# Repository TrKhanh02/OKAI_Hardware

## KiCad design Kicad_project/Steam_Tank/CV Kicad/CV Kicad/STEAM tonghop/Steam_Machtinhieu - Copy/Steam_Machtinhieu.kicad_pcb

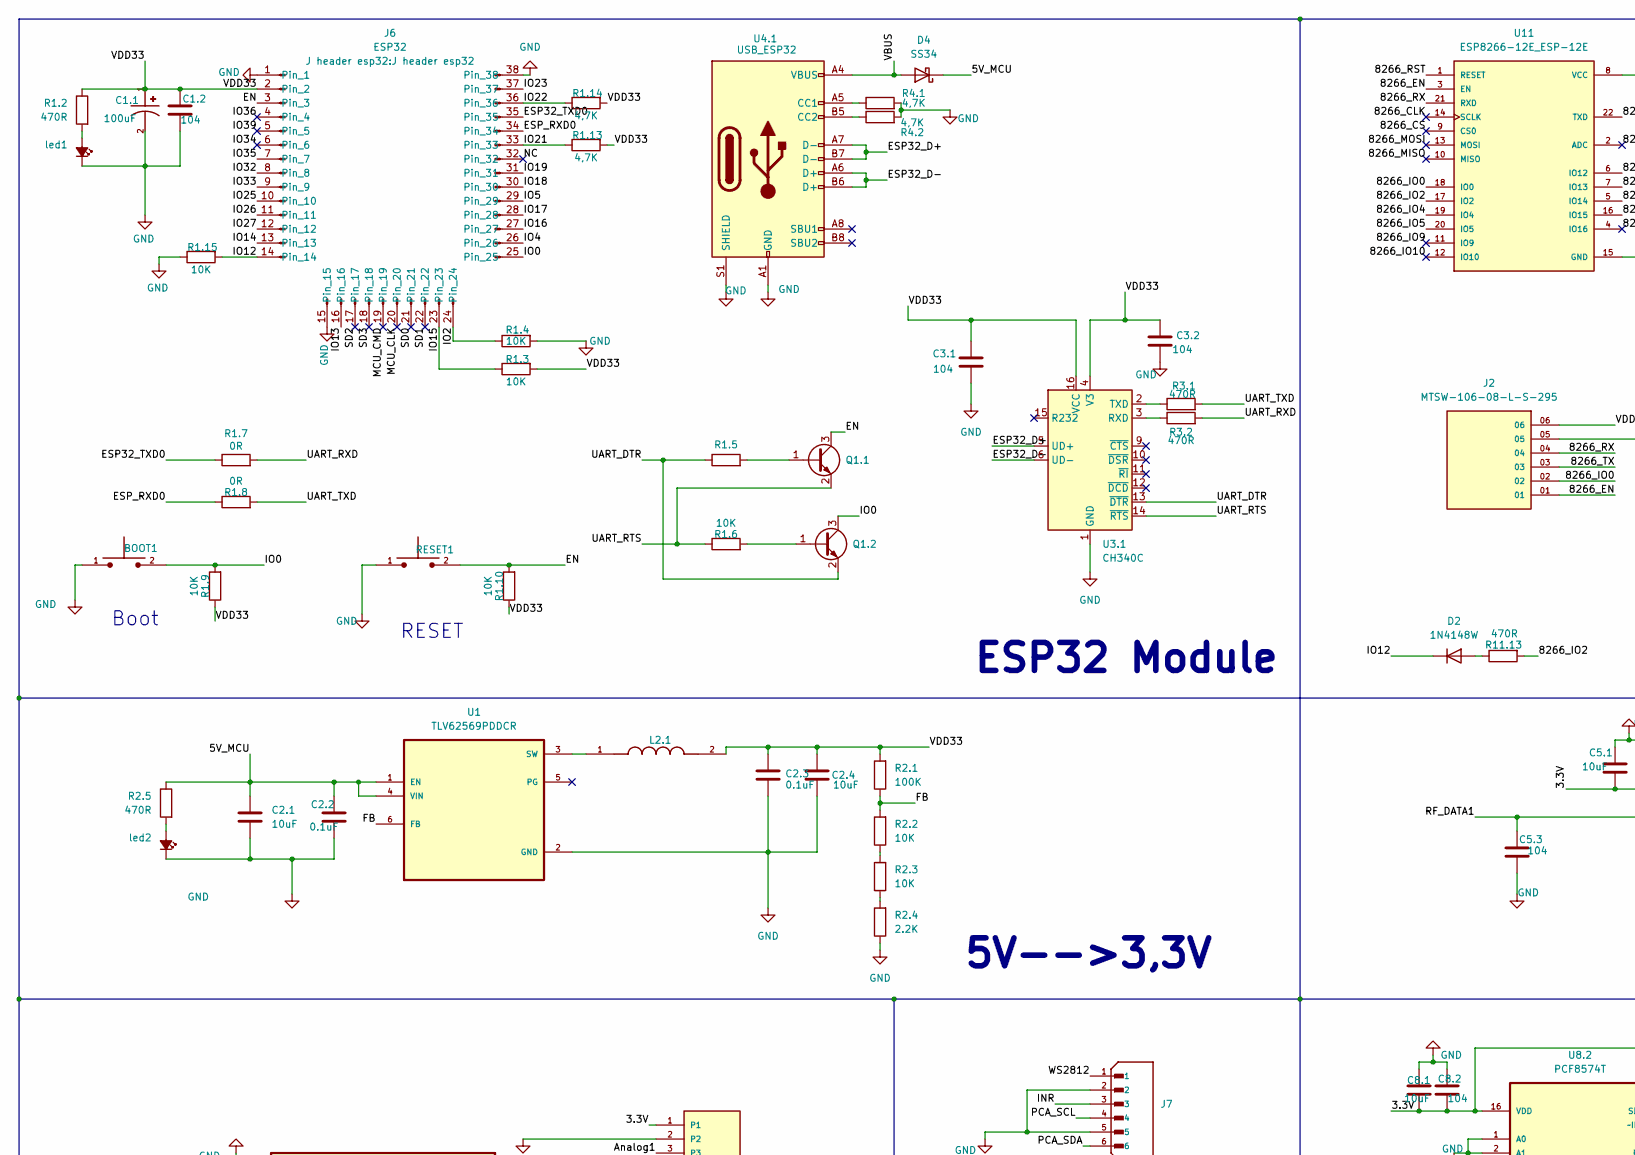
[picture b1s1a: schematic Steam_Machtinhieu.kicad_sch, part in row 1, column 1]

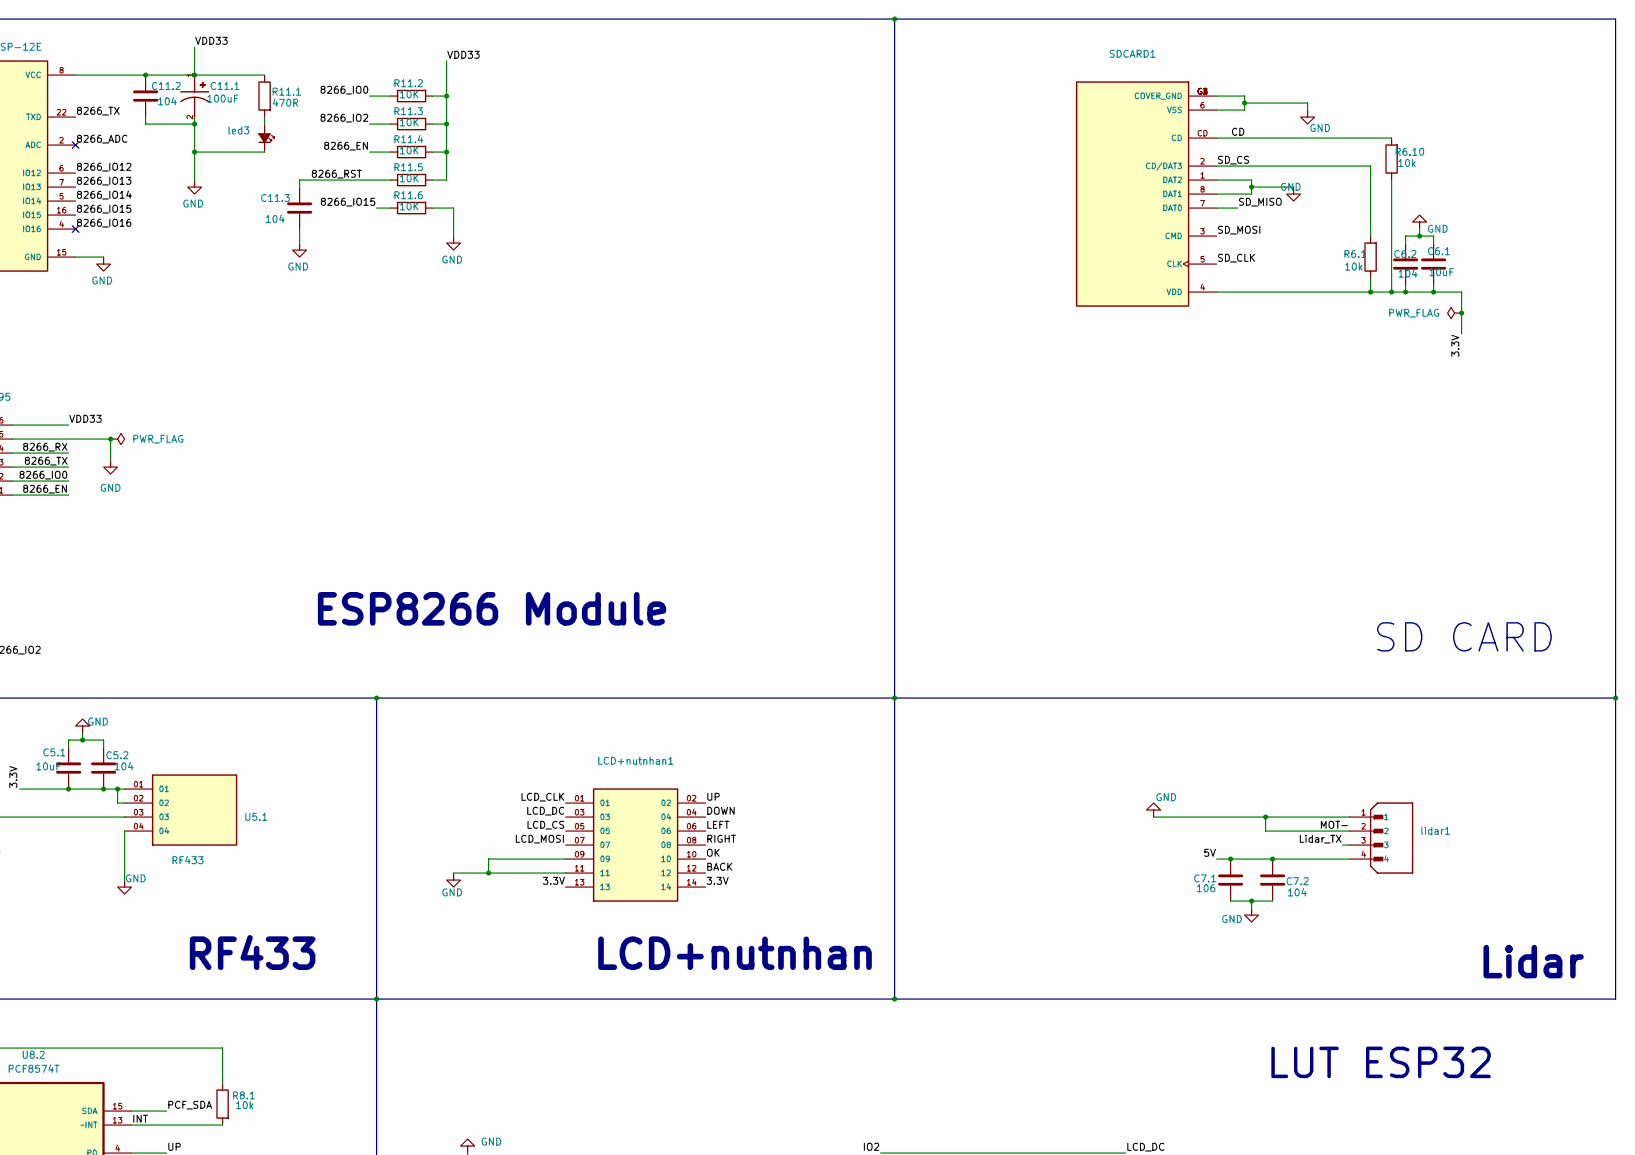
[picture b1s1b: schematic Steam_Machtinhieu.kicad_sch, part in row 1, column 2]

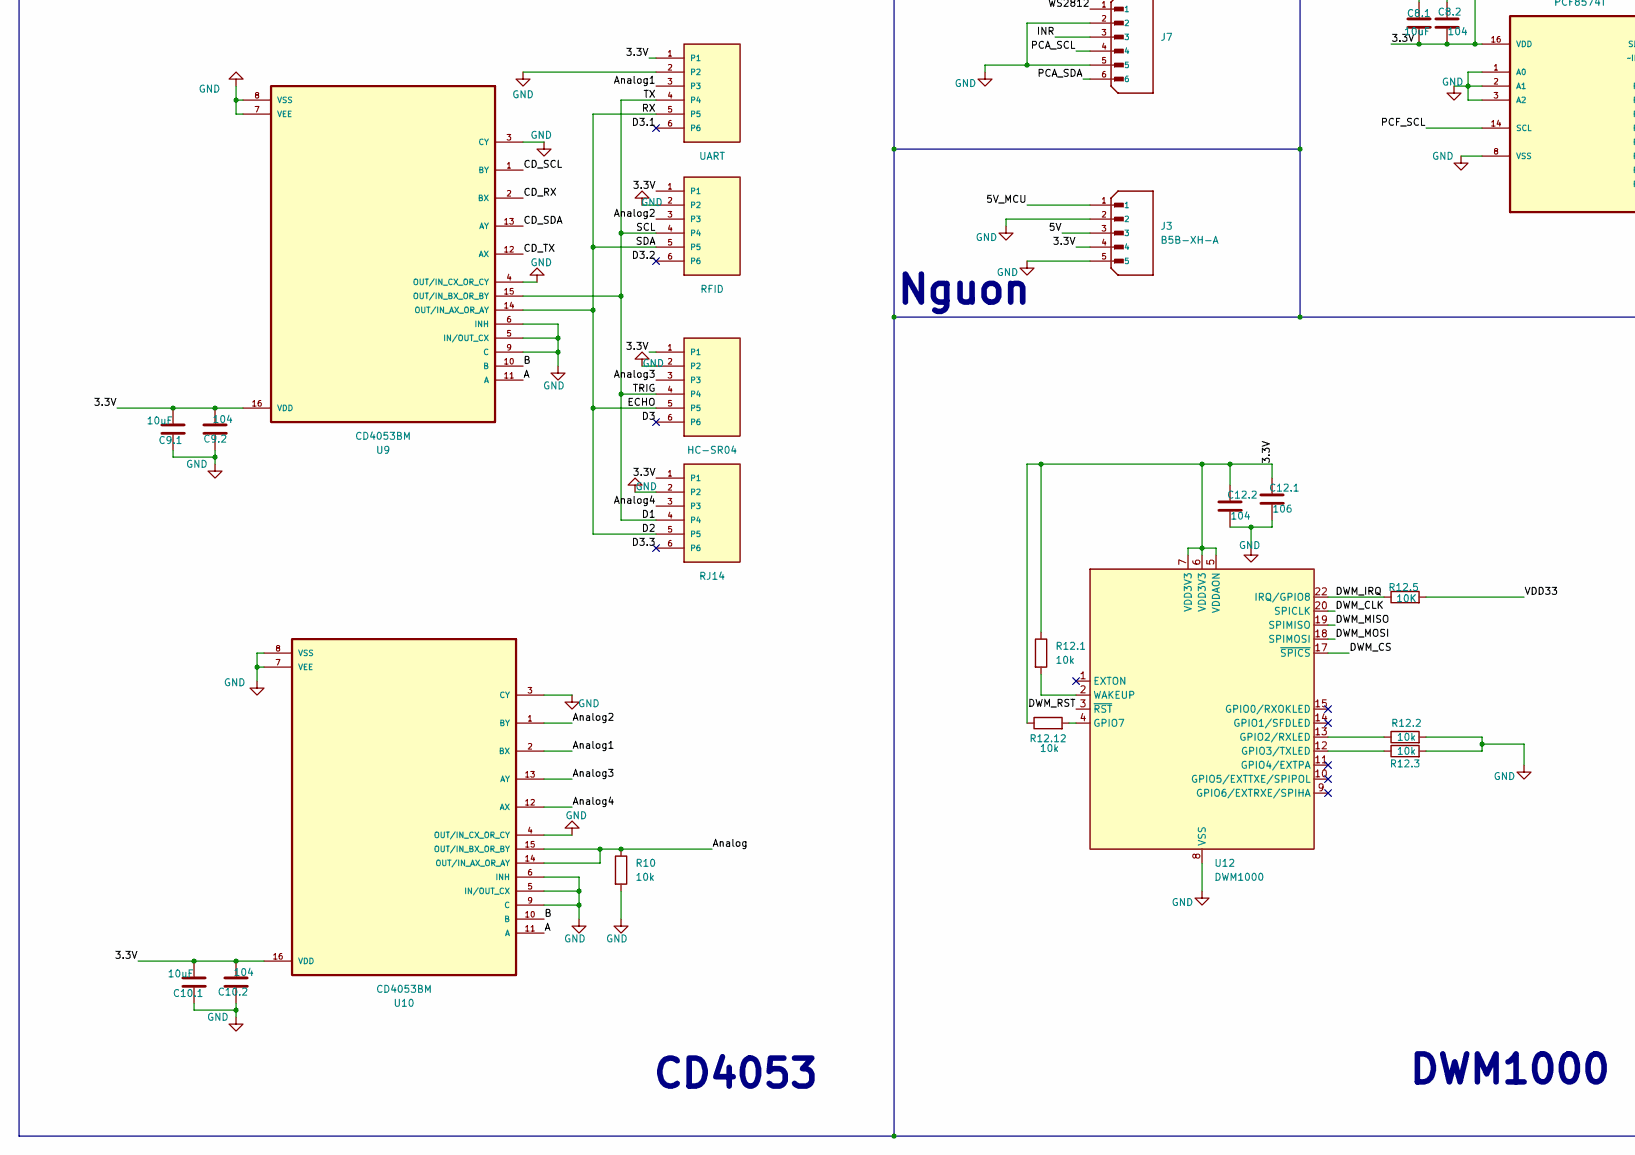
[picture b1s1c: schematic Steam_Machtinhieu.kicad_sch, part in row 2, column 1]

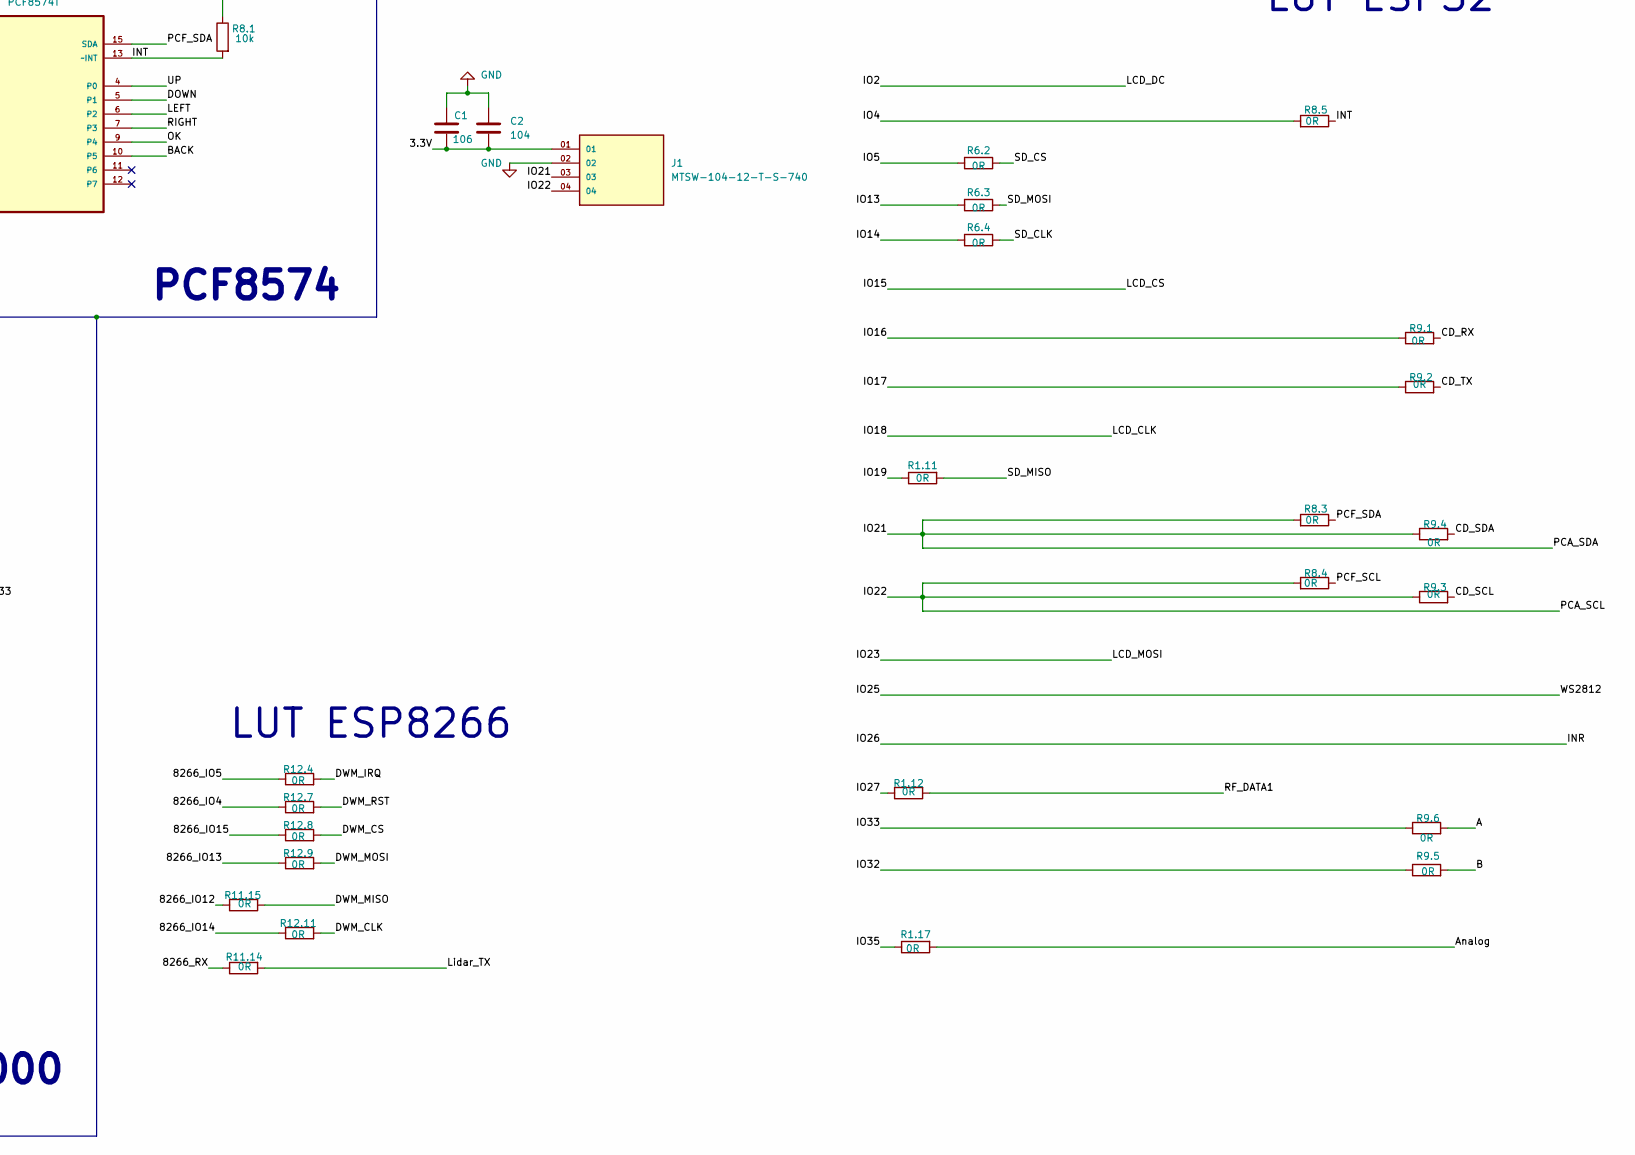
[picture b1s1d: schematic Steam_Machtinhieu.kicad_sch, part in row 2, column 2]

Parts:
BOOT1: TS10-63-26-BE-250-SMT-TR; SW_TS10-63-26-BE-250-SMT-TR; PARTREV 1.0
C1, C7.1, C12.1: 106; C_0805_2012Metric_Pad1.18x1.45mm_HandSolder
C1.1, C11.1: 100uF; CAPMP3216X180N; PARTREV 031320
C1.2, C2, C3.1, C3.2, C5.2, C5.3, C6.2, C7.2, C8.2, C9.2, C10.2, C11.2, C11.3, C12.2: 104; C_0805_2012Metric_Pad1.18x1.45mm_HandSolder
C2.1, C2.4: 10uF; C_0805_2012Metric
C2.2, C2.3: 0.1uF; C_0805_2012Metric
C5.1, C6.1, C8.1, C9.1, C10.1: 10uF; C_0805_2012Metric_Pad1.18x1.45mm_HandSolder
D2: 1N4148W; D_SOD-123
D4: SS34; D_SMA
J1: MTSW-104-12-T-S-740; SAMTEC_MTSW-104-12-T-S-740; PARTREV R
J2: MTSW-106-08-L-S-295; SAMTEC_MTSW-106-08-L-S-295; PARTREV R
J3: B5B-XH-A; JST_B5B-XH-A; PARTREV 7/4/21
J6: ESP32; J header esp32
J7: B6B-XH-A_LF__SN_; JST_B6B-XH-A_LF__SN_; PARTREV 7/4/21
L2.1: SLF7032T-331MR22-2PF; IND_SLF7032T-331MR22-2PF; PARTREV N/A
LCD+nutnhan1: MTLW-107-07-G-D-230; SAMTEC_MTLW-107-07-G-D-230; PARTREV R
Q1.1, Q1.2: SS8050; SOT-23
R1.2, R2.5, R3.1, R3.2, R11.1, R11.13: 470R; R_0805_2012Metric_Pad1.20x1.40mm_HandSolder
R1.3, R1.4, R1.5, R1.6, R1.9, R1.10, R1.15, R11.2, R11.3, R11.4, R11.5, R11.6, R12.5: 10K; R_0805_2012Metric_Pad1.20x1.40mm_HandSolder
R1.7, R1.8, R1.11, R1.12, R1.17, R6.2, R6.3, R6.4, R8.3, R8.4, R8.5, R9.1, R9.2, R9.3, R9.4, R9.5, R9.6, R11.14, R11.15, R12.4, R12.7, R12.8, R12.9, R12.11: 0R; R_0805_2012Metric_Pad1.20x1.40mm_HandSolder
R1.13, R1.14, R4.1, R4.2: 4,7K; R_0805_2012Metric_Pad1.20x1.40mm_HandSolder
R2.1: 100K; R_0805_2012Metric
R2.2, R2.3: 10K; R_0805_2012Metric
R2.4: 2.2K; R_0805_2012Metric
R6.1, R6.10, R8.1, R10, R12.1, R12.2, R12.3, R12.12: 10k; R_0805_2012Metric_Pad1.20x1.40mm_HandSolder
R11: UART; TE_RJ11-6N-B; PART_DESCRIPTION CONN MOD JACK 6P6C R/A UNSHLD
R12: RFID; TE_RJ11-6N-B; PART_DESCRIPTION CONN MOD JACK 6P6C R/A UNSHLD
RESET1: TS10-63-26-BE-250-SMT-TR; SW_TS10-63-26-BE-250-SMT-TR; PARTREV 1.0
RF433: U5.1; SAMTEC_MTSW-104-12-T-S-740; PARTREV R
RJ13, RJ14: HC-SR04; TE_RJ11-6N-B; PART_DESCRIPTION CONN MOD JACK 6P6C R/A UNSHLD
SDCARD1: MSD-1-A; CUI_MSD-1-A; PARTREV 1.0
U1: TLV62569PDDCR; SOT95P280X110-6N
U3.1: CH340C; SOIC-16_3.9x9.9mm_P1.27mm
U4.1: USB_ESP32; USB_C_Receptacle_HRO_TYPE-C-31-M-12
U8.2: PCF8574T; SOIC127P1032X265-16N; MPN PCF8574T
U9, U10: CD4053BM; SOIC127P600X175-16N
U11: ESP8266-12E_ESP-12E; XCVR_ESP8266-12E_ESP-12E
U12: DWM1000
led1, led2, led3: LED_Small_Filled; LED_0805_2012Metric_Pad1.15x1.40mm_HandSolder
lidar1: B4B-XH-A; JST_B4B-XH-A; PARTREV 7/4/21

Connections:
/3.3V: C1.2, C2.2, C5.1.2, C5.2.2, C6.1.1, C6.2.1, C8.1.1, C8.2.1, C9.1.1, C9.2.1, C10.1.1, C10.2.1, C12.1.1, C12.2.1, J1.01, J3.4, LCD+nutnhan1.13, LCD+nutnhan1.14, R6.1.1, R6.10.1, R8.1.1, R11.1, R12.1, R12.1.1, R12.12.1, RF433.01, RF433.02, RJ13.1, RJ14.1, SDCARD1.4 (VDD), U8.2.16 (VDD), U9.16 (VDD), U10.16 (VDD), U12.5 (VDDAON), U12.6 (VDD3V3), U12.7 (VDD3V3)
/5V: C7.1.1, C7.2.1, J3.3, lidar1.4
/5V_MCU: C2.1.1, C2.2.1, D4.1 (K), J3.1, R2.5.1, U1.1 (EN), U1.4 (VIN)
/8266_ADC: U11.2 (ADC)
/8266_CLK: U11.14 (SCLK)
/8266_CS: U11.9 (CS0)
/8266_EN: J2.01, R11.4.1, U11.3 (EN)
/8266_IO0: J2.02, R11.2.1, U11.18 (IO0)
/8266_IO2: R11.3.1, R11.13.2, U11.17 (IO2)
/8266_IO4: R12.7.1, U11.19 (IO4)
/8266_IO5: R12.4.1, U11.20 (IO5)
/8266_IO9: U11.11 (IO9)
/8266_IO10: U11.12 (IO10)
/8266_IO12: R11.15.1, U11.6 (IO12)
/8266_IO13: R12.9.1, U11.7 (IO13)
/8266_IO14: R12.11.1, U11.5 (IO14)
/8266_IO15: R11.6.1, R12.8.1, U11.16 (IO15)
/8266_IO16: U11.4 (IO16)
/8266_MISO: U11.10 (MISO)
/8266_MOSI: U11.13 (MOSI)
/8266_RST: C11.3.1, R11.5.1, U11.1 (RESET)
/8266_RX: J2.04, R11.14.1, U11.21 (RXD)
/8266_TX: J2.03, U11.22 (TXD)
/A: R9.6.2, U9.11 (A), U10.11 (A)
/Analog: R1.17.2, R10.1, U10.14 (OUT/IN_AX_OR_AY), U10.15 (OUT/IN_BX_OR_BY)
/Analog1: R11.3, U10.2 (BX)
/Analog2: R12.3, U10.1 (BY)
/Analog3: RJ13.3, U10.13 (AY)
/Analog4: RJ14.3, U10.12 (AX)
/B: R9.5.2, U9.10 (B), U10.10 (B)
/BACK: LCD+nutnhan1.12, U8.2.10 (P5)
/CD: R6.10.2, SDCARD1.CD
/CD_RX: R9.1.2, U9.2 (BX)
/CD_SCL: R9.3.2, U9.1 (BY)
/CD_SDA: R9.4.2, U9.13 (AY)
/CD_TX: R9.2.2, U9.12 (AX)
/D1: R11.4, R12.4, RJ13.4, RJ14.4, U9.15 (OUT/IN_BX_OR_BY)
/D2: R11.5, R12.5, RJ13.5, RJ14.5, U9.14 (OUT/IN_AX_OR_AY)
/D3: RJ13.6
/D3.1: R11.6
/D3.2: R12.6
/D3.3: RJ14.6
/DOWN: LCD+nutnhan1.04, U8.2.5 (P1)
/DWM_CLK: R12.11.2, U12.20 (SPICLK)
/DWM_CS: R12.8.2, U12.17 (~SPICS)
/DWM_IRQ: R12.4.2, R12.5.1, U12.22 (IRQ/GPIO8)
/DWM_MISO: R11.15.2, U12.19 (SPIMISO)
/DWM_MOSI: R12.9.2, U12.18 (SPIMOSI)
/DWM_RST: R12.7.2, U12.3 (~RST)
/EN: J6.3, Q1.1.3 (C), R1.10.2, RESET1.2
/ESP32_D+: U3.1.5 (UD+), U4.1.A7 (D-), U4.1.B7 (D-)
/ESP32_D-: U3.1.6 (UD-), U4.1.A6 (D+), U4.1.B6 (D+)
/ESP32_TXD0: J6.35, R1.7.1
/ESP_RXD0: J6.34, R1.8.1
/FB: R2.1.1, R2.2.2, U1.6 (FB)
/INR: J6.11, J7.3
/INT: R8.1.2, R8.5.1, U8.2.13 (~INT)
/IO0: BOOT1.2, J6.25, Q1.2.3 (C), R1.9.2
/IO2: J6.24, LCD+nutnhan1.03, R1.4.1
/IO4: J6.26, R8.5.2
/IO5: J6.29, R6.2.2
/IO12: D2.1 (K), J6.14, R1.15.2
/IO13: J6.16, R6.3.2
/IO14: J6.13, R6.4.2
/IO15: J6.23, LCD+nutnhan1.05, R1.3.1
/IO16: J6.27, R9.1.1
/IO17: J6.28, R9.2.1
/IO18: J6.30, LCD+nutnhan1.01
/IO19: J6.31, R1.11.1
/IO21: J1.03, J6.33, J7.6, R1.13.1, R8.3.2, R9.4.1
/IO22: J1.04, J6.36, J7.4, R1.14.1, R8.4.2, R9.3.1
/IO23: J6.37, LCD+nutnhan1.07
/IO25: J6.10, J7.1
/IO27: J6.12, R1.12.1
/IO32: J6.8, R9.5.1
/IO33: J6.9, R9.6.1
/IO34: J6.6
/IO35: J6.7, R1.17.1
/IO36: J6.4
/IO39: J6.5
/LEFT: LCD+nutnhan1.06, U8.2.6 (P2)
/Lidar_TX: R11.14.2, lidar1.3
/MCU_CLK: J6.20
/MCU_CMD: J6.19
/NC: J6.32
/OK: LCD+nutnhan1.10, U8.2.9 (P4)
/PCF_SCL: R8.4.1, U8.2.14 (SCL)
/PCF_SDA: R8.3.1, U8.2.15 (SDA)
/RF_DATA1: C5.3.1, R1.12.2, RF433.03
/RIGHT: LCD+nutnhan1.08, U8.2.7 (P3)
/SD0: J6.21
/SD1: J6.22
/SD2: J6.17
/SD3: J6.18
/SD_CLK: R6.4.1, SDCARD1.5 (CLK)
/SD_CS: R6.1.2, R6.2.1, SDCARD1.2 (CD/DAT3)
/SD_MISO: R1.11.2, SDCARD1.7 (DAT0)
/SD_MOSI: R6.3.1, SDCARD1.3 (CMD)
/UART_DTR: Q1.2.2 (E), R1.5.1, U3.1.13 (~DTR)
/UART_RTS: Q1.1.2 (E), R1.6.1, U3.1.14 (~RTS)
/UART_RXD: R1.7.2, R3.2.2
/UART_TXD: R1.8.2, R3.1.2
/UP: LCD+nutnhan1.02, U8.2.4 (P0)
/VBUS: D4.2 (A), U4.1.A4 (VBUS), U4.1.A9 (VBUS), U4.1.B4 (VBUS), U4.1.B9 (VBUS)
/VDD33: C1.1.1, C1.2.1, C2.3.1, C2.4.1, C3.1.2, C3.2.2, C11.1.1, C11.2.1, J2.06, J6.2, L2.1.2, R1.2.1, R1.3.2, R1.9.1, R1.10.1, R1.13.2, R1.14.2, R2.1.2, R11.1.1, R11.2.2, R11.3.2, R11.4.2, R11.5.2, R12.5.2, U3.1.4 (V3), U3.1.16 (VCC), U11.8 (VCC)
GND: BOOT1.1, C1.1, C1.1.2, C1.2.2, C2.1, C2.1.2, C2.2.2, C2.3.2, C2.4.2, C3.1.1, C3.2.1, C5.1.1, C5.2.1, C5.3.2, C6.1.2, C6.2.2, C7.1.2, C7.2.2, C8.1.2, C8.2.2, C9.1.2, C9.2.2, C10.1.2, C10.2.2, C11.1.2, C11.2.2, C11.3.2, C12.1.2, C12.2.2, J1.02, J2.05, J3.2, J3.5, J6.1, J6.15, J6.38, J7.2, J7.5, LCD+nutnhan1.09, LCD+nutnhan1.11, R1.4.2, R1.15.1, R2.4.1, R4.1.2, R4.2.2, R10.2, R11.2, R11.6.2, R12.2, R12.2.2, R12.3.2, RESET1.1, RF433.04, RJ13.2, RJ14.2, SDCARD1.1 (DAT2), SDCARD1.6 (VSS), SDCARD1.8 (DAT1), SDCARD1.G1 (COVER_GND), SDCARD1.G2 (COVER_GND), SDCARD1.G3 (COVER_GND), SDCARD1.G4 (COVER_GND), U1.2 (GND), U3.1.1 (GND), U4.1.A1 (GND), U4.1.A12 (GND), U4.1.B1 (GND), U4.1.B12 (GND), U4.1.S1 (SHIELD), U8.2.1 (A0), U8.2.2 (A1), U8.2.3 (A2), U8.2.8 (VSS), U9.3 (CY), U9.4 (OUT/IN_CX_OR_CY), U9.5 (IN/OUT_CX), U9.6 (INH), U9.7 (VEE), U9.8 (VSS), U9.9 (C), U10.3 (CY), U10.4 (OUT/IN_CX_OR_CY), U10.5 (IN/OUT_CX), U10.6 (INH), U10.7 (VEE), U10.8 (VSS), U10.9 (C), U11.15 (GND), U12.8 (VSS), U12.16 (VSS), U12.21 (VSS), U12.23 (VSS), U12.24 (VSS), led1.1 (K), led2.1 (K), led3.1 (K), lidar1.1, lidar1.2
unnamed: D2.2 (A), R11.13.1
unnamed: Q1.1.1 (B), R1.5.2
unnamed: Q1.2.1 (B), R1.6.2
unnamed: R2.2.1, R2.3.2
unnamed: R2.3.1, R2.4.2
unnamed: L2.1.1, U1.3 (SW)
unnamed: R3.2.1, U3.1.3 (RXD)
unnamed: R3.1.1, U3.1.2 (TXD)
unnamed: R4.1.1, U4.1.A5 (CC1)
unnamed: R4.2.1, U4.1.B5 (CC2)
unnamed: R12.2.1, U12.13 (GPIO2/RXLED)
unnamed: R12.3.1, U12.12 (GPIO3/TXLED)
unnamed: R12.12.2, U12.4 (GPIO7)
unnamed: R12.1.2, U12.2 (WAKEUP)
unnamed: R1.2.2, led1.2 (A)
unnamed: R2.5.2, led2.2 (A)
unnamed: R11.1.2, led3.2 (A)

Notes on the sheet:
Lidar
CD4053
RESET
Boot
DWM1000
LUT ESP32
RF433
ESP32 Module
LUT ESP8266
SD CARD
PCF8574
ESP8266 Module
Nguon
LCD+nutnhan
5V-->3,3V

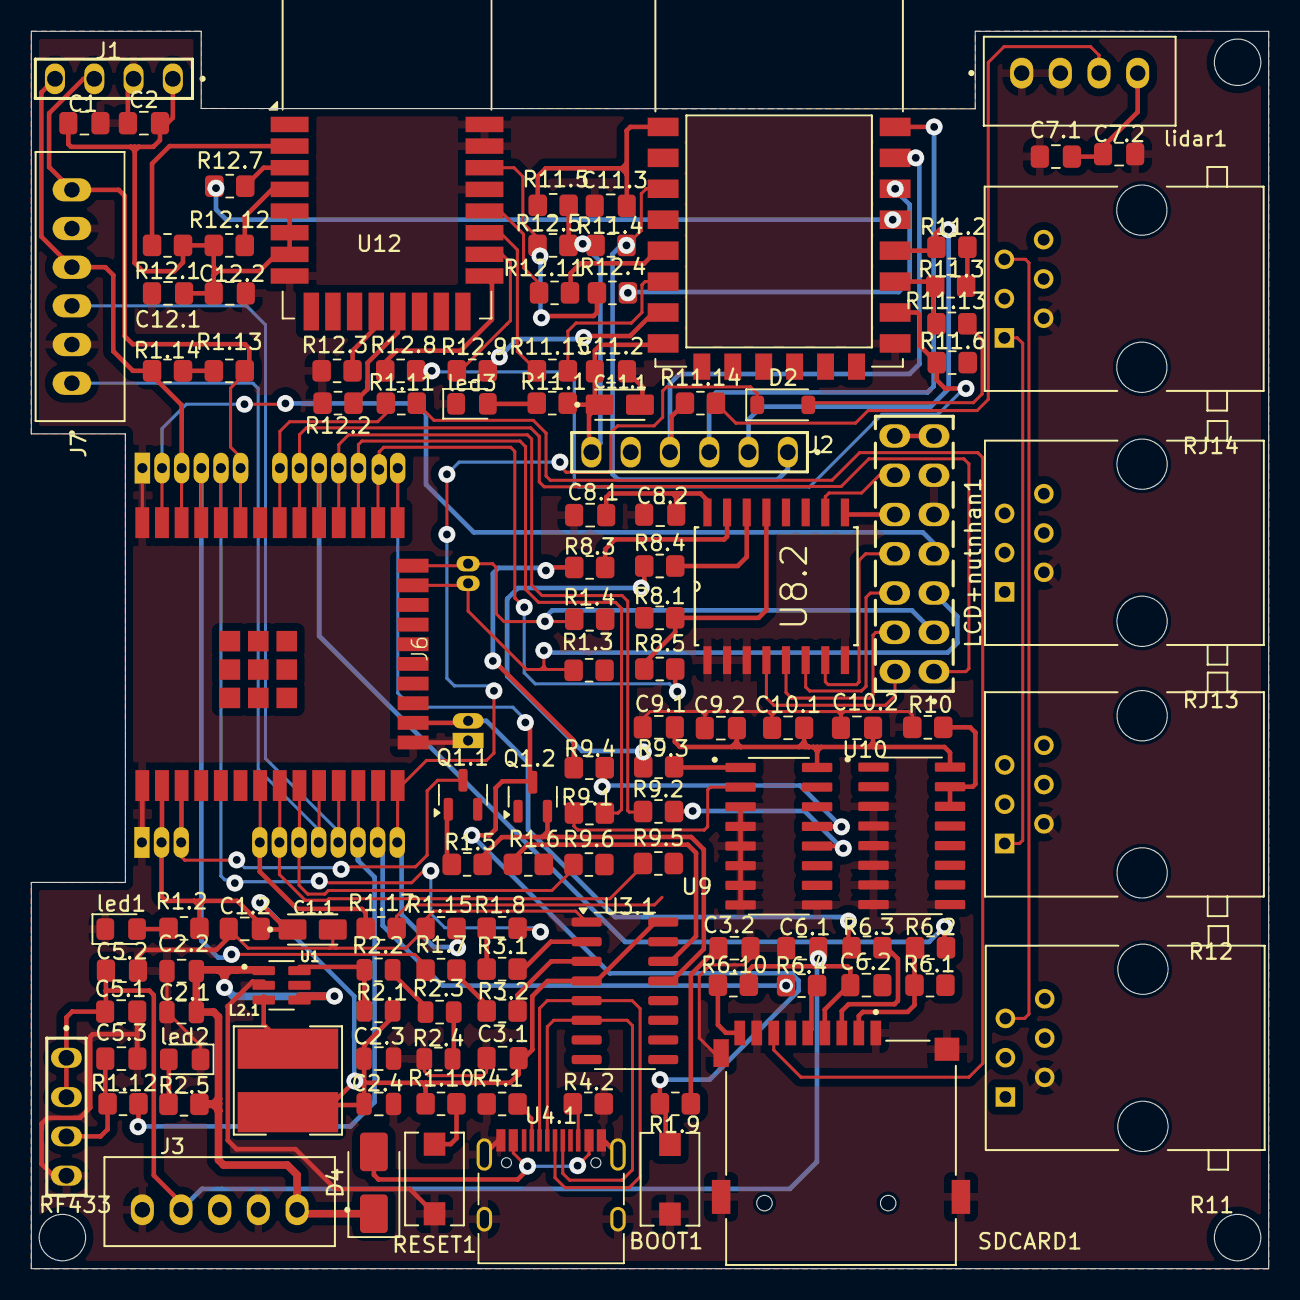
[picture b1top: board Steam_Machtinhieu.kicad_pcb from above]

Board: 2 copper layers, 80.0 x 80.0 mm, 118 parts (0 on the bottom side), 101 nets.

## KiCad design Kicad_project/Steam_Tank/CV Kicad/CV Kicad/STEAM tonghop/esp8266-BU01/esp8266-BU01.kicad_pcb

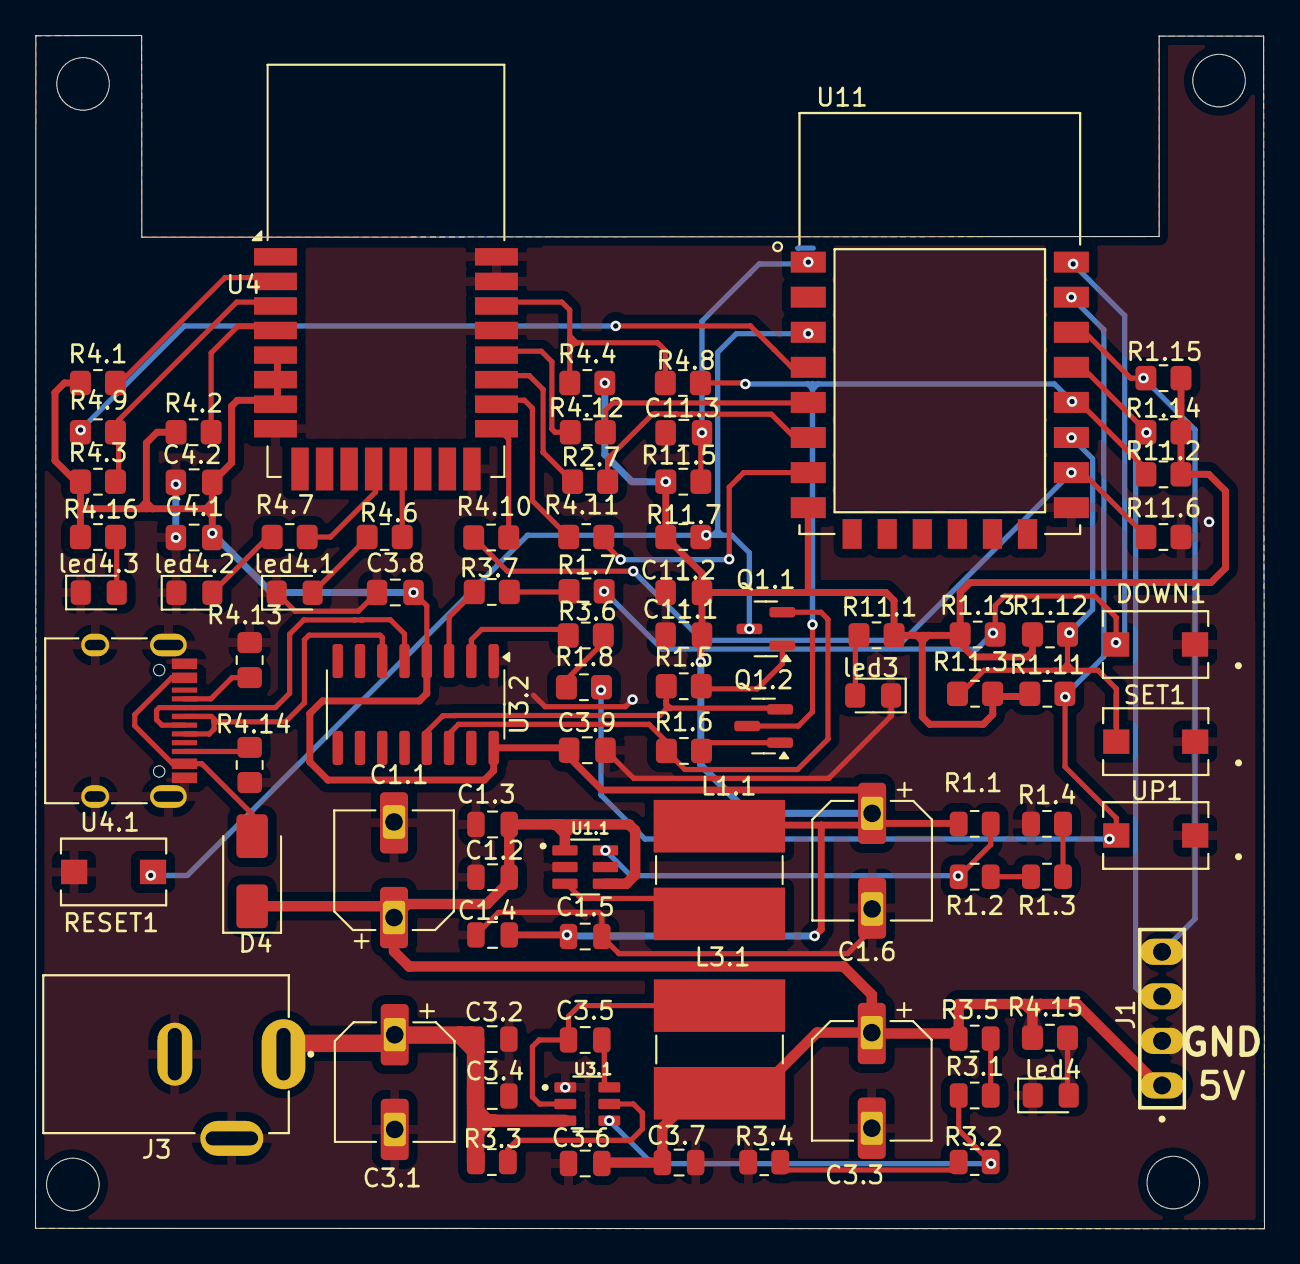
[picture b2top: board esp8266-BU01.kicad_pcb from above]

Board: 2 copper layers, 70.1 x 68.0 mm, 84 parts (0 on the bottom side), 55 nets.

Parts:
C1.1, C1.6, C3.1, C3.3: 220uF; CP_Elec_6.3x7.7
C1.2, C1.5, C3.2, C3.7: 10uF; C_0805_2012Metric
C1.3, C1.4, C3.4, C3.5, C3.6: 0.1uF; C_0805_2012Metric
C3.8, C3.9, C4.2, C11.2, C11.3: 104; C_0805_2012Metric_Pad1.18x1.45mm_HandSolder
C4.1, C11.1: 106; C_0805_2012Metric_Pad1.18x1.45mm_HandSolder
D4: SS34; D_SMA
DOWN1: TS10-63-26-BE-250-SMT-TR; SW_TS10-63-26-BE-250-SMT-TR
J1: MTSW-104-12-T-S-740; SAMTEC_MTSW-104-12-T-S-740
J3: PJ-035D; CUI_PJ-035D
L1.1, L3.1: 22uH; L_Ferrocore_DLG-0705
Q1.1, Q1.2: SS8050; SOT-23
R1.1, R3.1: 100K; R_0805_2012Metric
R1.2, R1.3, R3.2, R3.3, R3.4, R3.5: 10K; R_0805_2012Metric
R1.4: 3,3K; R_0805_2012Metric
R1.5, R1.6, R1.11, R1.12, R1.13, R1.14, R1.15, R4.3, R4.4, R11.2, R11.3, R11.5, R11.6, R11.7: 10K; R_0805_2012Metric_Pad1.20x1.40mm_HandSolder
R1.7, R1.8, R2.7, R4.8, R4.9, R4.10, R4.11, R4.12: 0R; R_0805_2012Metric_Pad1.20x1.40mm_HandSolder
R3.6, R3.7, R4.6, R4.7, R4.16, R11.1: 470R; R_0805_2012Metric_Pad1.20x1.40mm_HandSolder
R4.1, R4.2: 10k; R_0805_2012Metric_Pad1.20x1.40mm_HandSolder
R4.13, R4.14, R4.15: 4,7K; R_0805_2012Metric_Pad1.20x1.40mm_HandSolder
RESET1: TS10-63-26-BE-250-SMT-TR; SW_TS10-63-26-BE-250-SMT-TR
SET1: TS10-63-26-BE-250-SMT-TR; SW_TS10-63-26-BE-250-SMT-TR
U1.1: TLV62569PDDCR; SOT95P280X110-6N
U3.1: TPS563201DDCR; SOT95P280X110-6N
U3.2: CH340C; SOIC-16_3.9x9.9mm_P1.27mm
U4: DWM1000
U4.1: USB_ESP32; USB_C_Receptacle_HRO_TYPE-C-31-M-12
U11: ESP8266-12E_ESP-12E; XCVR_ESP8266-12E_ESP-12E
UP1: TS10-63-26-BE-250-SMT-TR; SW_TS10-63-26-BE-250-SMT-TR
led3, led4, led4.1, led4.2, led4.3: LED_Small_Filled; LED_0805_2012Metric_Pad1.15x1.40mm_HandSolder

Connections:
/5V: C1.1.1, C1.2.1, C1.3.1, C3.3.1, C3.6.1, C3.7.1, D4.1 (K), J1.01, L3.1.2, R3.5.2, R4.15.1, U1.1.1 (EN), U1.1.4 (VIN)
/12VDC: C3.1.1, C3.2.1, C3.4.1, J3.1, R3.3.2, U3.1.3 (VIN)
/8266_EN: Q1.1.3 (C), R11.7.2, RESET1.2, U11.3 (EN)
/8266_IO0: Q1.2.3 (C), R4.8.1, R11.2.1, U11.18 (IO0)
/8266_IO2: R1.12.2, R11.3.1, SET1.2, U11.17 (IO2)
/8266_IO4: J1.03, R1.14.1, U11.19 (IO4)
/8266_IO5: J1.04, R1.15.1, U11.20 (IO5)
/8266_IO12: R2.7.1, U11.6 (IO12)
/8266_IO13: R4.11.1, U11.7 (IO13)
/8266_IO14: R4.12.1, U11.5 (IO14)
/8266_IO15: R4.10.1, R11.6.1, U11.16 (IO15)
/8266_IO16: R4.9.1, U11.4 (IO16)
/8266_RST: C11.3.1, R11.5.1, U11.1 (RESET)
/8266_RX: R1.8.1, R1.11.2, U11.21 (RXD), UP1.2
/8266_TX: DOWN1.2, R1.7.1, R1.13.2, U11.22 (TXD)
/DWM_CLK: R4.12.2, U4.20 (SPICLK)
/DWM_CS: R4.10.2, U4.17 (~SPICS)
/DWM_IRQ: R4.4.1, R4.8.2, U4.22 (IRQ/GPIO8)
/DWM_MISO: R2.7.2, U4.19 (SPIMISO)
/DWM_MOSI: R4.11.2, U4.18 (SPIMOSI)
/DWM_RST: R4.3.2, R4.9.2, U4.3 (~RST)
/ESP32_D+: U3.2.5 (UD+), U4.1.A7 (D-), U4.1.B7 (D-)
/ESP32_D-: U3.2.6 (UD-), U4.1.A6 (D+), U4.1.B6 (D+)
/FB_U1.1: R1.1.1, R1.2.2, U1.1.6 (FB)
/UART_DTR: Q1.2.2 (E), R1.5.1, U3.2.13 (~DTR)
/UART_RTS: Q1.1.2 (E), R1.6.1, U3.2.14 (~RTS)
/UART_RXD: R1.7.2, R3.7.2
/UART_TXD: R1.8.2, R3.6.2
/VBUS: D4.2 (A), U4.1.A4 (VBUS), U4.1.A9 (VBUS), U4.1.B4 (VBUS), U4.1.B9 (VBUS)
/VDD33: C1.4.1, C1.5.1, C1.6.1, C3.8.2, C3.9.2, C4.1.1, C4.2.1, C11.1.1, C11.2.1, L1.1.1, R1.1.2, R1.11.1, R1.12.1, R1.13.1, R1.14.2, R1.15.2, R4.1.1, R4.2.1, R4.3.1, R4.4.2, R4.16.2, R11.1.1, R11.2.2, R11.3.2, R11.5.2, R11.7.1, U3.2.4 (V3), U3.2.16 (VCC), U4.5 (VDDAON), U4.6 (VDD3V3), U4.7 (VDD3V3), U11.8 (VCC)
GND: C1.1.2, C1.2.2, C1.3.2, C1.4.2, C1.5.2, C1.6.2, C3.1.2, C3.2.2, C3.3.2, C3.4.2, C3.6.2, C3.7.2, C3.8.1, C3.9.1, C4.1.2, C4.2.2, C11.1.2, C11.2.2, C11.3.2, DOWN1.1, J1.02, J3.2, J3.3, R1.4.1, R3.4.1, R4.13.2, R4.14.2, R11.6.2, RESET1.1, SET1.1, U1.1.2 (GND), U3.1.1 (GND), U3.2.1 (GND), U4.8 (VSS), U4.16 (VSS), U4.21 (VSS), U4.23 (VSS), U4.24 (VSS), U4.1.A1 (GND), U4.1.A12 (GND), U4.1.B1 (GND), U4.1.B12 (GND), U4.1.S1 (SHIELD), U11.15 (GND), UP1.1, led3.1 (K), led4.1 (K), led4.1.1 (K), led4.2.1 (K), led4.3.1 (K)
unnamed: Q1.1.1 (B), R1.5.2
unnamed: Q1.2.1 (B), R1.6.2
unnamed: R1.2.1, R1.3.2
unnamed: R1.3.1, R1.4.2
unnamed: R3.1.2, R3.5.1
unnamed: R3.2.1, R3.4.2
unnamed: L1.1.2, U1.1.3 (SW)
unnamed: R3.3.1, U3.1.5 (EN)
unnamed: C3.5.1, L3.1.1, U3.1.2 (SW)
unnamed: C3.5.2, U3.1.6 (VBST)
unnamed: R3.1.1, R3.2.2, U3.1.4 (VFB)
unnamed: R3.7.1, U3.2.3 (RXD)
unnamed: R3.6.1, U3.2.2 (TXD)
unnamed: R4.6.1, U4.13 (GPIO2/RXLED)
unnamed: R4.7.1, U4.12 (GPIO3/TXLED)
unnamed: R4.2.2, U4.4 (GPIO7)
unnamed: R4.1.2, U4.2 (WAKEUP)
unnamed: R4.13.1, U4.1.A5 (CC1)
unnamed: R4.14.1, U4.1.B5 (CC2)
unnamed: R11.1.2, led3.2 (A)
unnamed: R4.15.2, led4.2 (A)
unnamed: R4.6.2, led4.1.2 (A)
unnamed: R4.7.2, led4.2.2 (A)
unnamed: R4.16.1, led4.3.2 (A)

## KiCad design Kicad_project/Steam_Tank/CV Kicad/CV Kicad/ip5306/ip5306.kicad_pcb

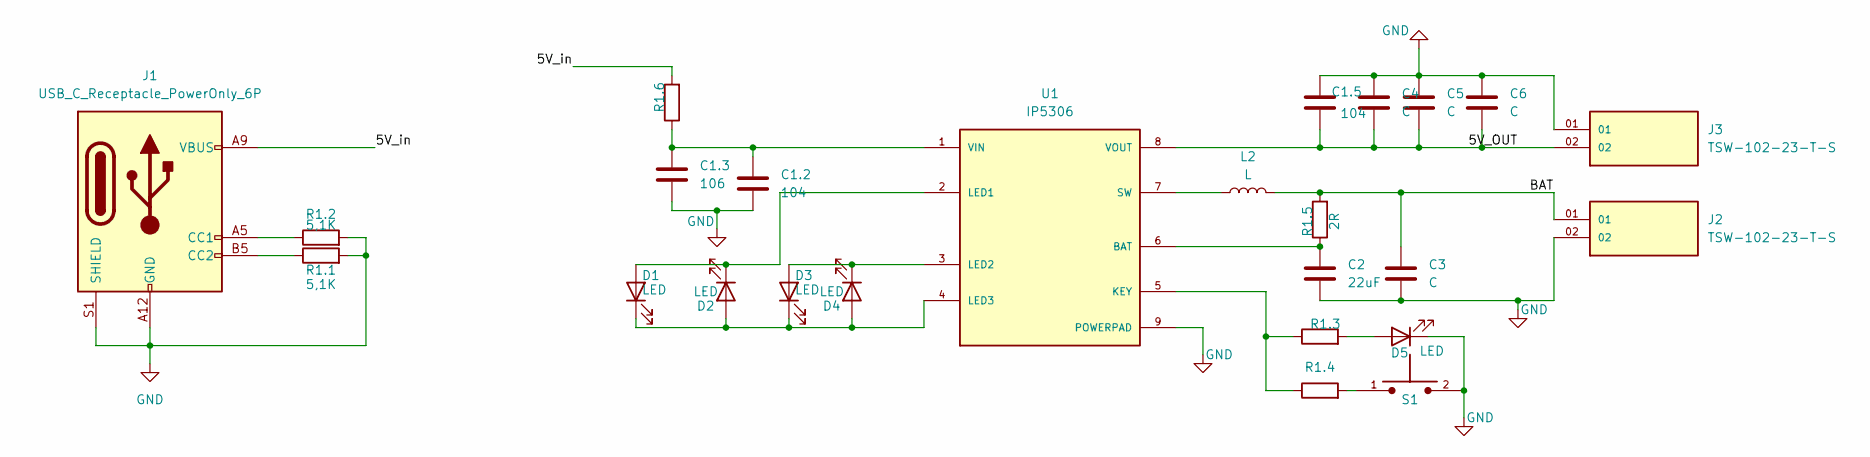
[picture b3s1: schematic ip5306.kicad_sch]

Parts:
C1.2, C1.5: 104; C_0805_2012Metric_Pad1.18x1.45mm_HandSolder
C1.3: 106; C_0805_2012Metric_Pad1.18x1.45mm_HandSolder
C2: 22uF; C_1206_3216Metric_Pad1.33x1.80mm_HandSolder
C3, C4, C5, C6: C; C_1206_3216Metric_Pad1.33x1.80mm_HandSolder
D1, D2, D3, D4, D5: LED; LED_0805_2012Metric_Pad1.15x1.40mm_HandSolder
J1: USB_C_Receptacle_PowerOnly_6P; USB_C_Receptacle_GCT_USB4125-xx-x_6P_TopMnt_Horizontal
J2, J3: TSW-102-23-T-S; SAMTEC_TSW-102-23-T-S; PARTREV R
L2: L; L_7.3x7.3_H4.5
R1.1, R1.2: 5,1K; R_0805_2012Metric_Pad1.20x1.40mm_HandSolder
R1.3, R1.4, R1.6: R_0805_2012Metric_Pad1.20x1.40mm_HandSolder
R1.5: 2R; R_0805_2012Metric_Pad1.20x1.40mm_HandSolder
S1: TS10-63-26-BE-250-SMT-TR; SW_TS10-63-26-BE-250-SMT-TR; PARTREV 1.0
U1: IP5306; SOP127P600X165-9N; PARTREV 1.31

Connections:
/5V_OUT: C1.5.2, C4.2, C5.2, C6.2, J3.02, U1.8 (VOUT)
/5V_in: J1.A9 (VBUS), J1.B9 (VBUS), R1.6.2
/BAT: C3.1, J2.01, L2.2, R1.5.2
GND: C1.2.2, C1.3.2, C1.5.1, C2.2, C3.2, C4.1, C5.1, C6.1, D5.1 (K), J1.A12 (GND), J1.B12 (GND), J1.S1 (SHIELD), J2.02, J3.01, R1.1.2, R1.2.2, S1.2, U1.9 (POWERPAD)
unnamed: D1.2 (A), D2.1 (K), U1.2 (LED1)
unnamed: D1.1 (K), D2.2 (A), D3.1 (K), D4.2 (A), U1.4 (LED3)
unnamed: D3.2 (A), D4.1 (K), U1.3 (LED2)
unnamed: D5.2 (A), R1.3.2
unnamed: J1.A5 (CC1), R1.2.1
unnamed: J1.B5 (CC2), R1.1.1
unnamed: R1.4.2, S1.1
unnamed: C2.1, R1.5.1, U1.6 (BAT)
unnamed: R1.3.1, R1.4.1, U1.5 (KEY)
unnamed: L2.1, U1.7 (SW)
unnamed: C1.2.1, C1.3.1, R1.6.1, U1.1 (VIN)

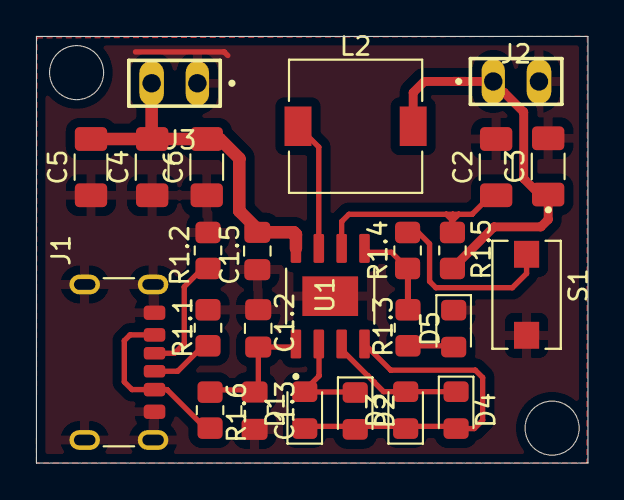
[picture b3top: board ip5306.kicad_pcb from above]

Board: 2 copper layers, 30.6 x 23.7 mm, 25 parts (0 on the bottom side), 15 nets.
